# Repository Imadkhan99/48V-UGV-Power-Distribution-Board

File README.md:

# 48V-UGV-Power-Distribution-Board
48 V high-current power distribution PCB for a 4-wheel UGV, featuring MOSFET high-side switching and a two-layer KiCad design.
# 48 V UGV Power Distribution Board

### Project Overview

This project focuses on the electrical design and PCB layout of a high-current Power Distribution Board (PDB) for a four-wheel autonomous Unmanned Ground Vehicle (UGV) intended for vineyard applications.

The objective is to develop a compact power distribution architecture capable of supplying multiple motor controllers and auxiliary loads from a nominal 48 V battery system.

### Key Design Specifications

| Parameter | Design Target |
|---|---|
| Input Voltage | 48 V DC nominal |
| System Power | Approximately 5 kW |
| Maximum Bus Current | 100 A |
| Motor Controller Channels | 4 |
| Switching Architecture | P-channel MOSFET high-side switching |
| MOSFET | Vishay SUM70101EL-GE3 |
| Gate Control | Discrete BJT driver |
| PCB Configuration | 2 layers, 200 × 100 mm |
| Design Software | KiCad 9 |

### Engineering Focus

- Design of high-current DC power distribution circuits.
- Implementation of discrete MOSFET switching architecture.
- High-current PCB routing and copper-zone design.
- Component selection based on electrical requirements.
- Connector placement and power/ground layout.
- Thermal management considerations and via stitching.

### Development Status

**Design-stage project:** Initial PCB layout and routing have been completed. Formal electrical verification, fabrication, thermal validation, and hardware testing are not yet documented.

The published specifications represent design objectives rather than verified hardware ratings.

### Tools and Technologies

KiCad 9, Power Electronics, PCB Layout, MOSFET Switching, DC Power Distribution, and Robotics Electrical Systems.

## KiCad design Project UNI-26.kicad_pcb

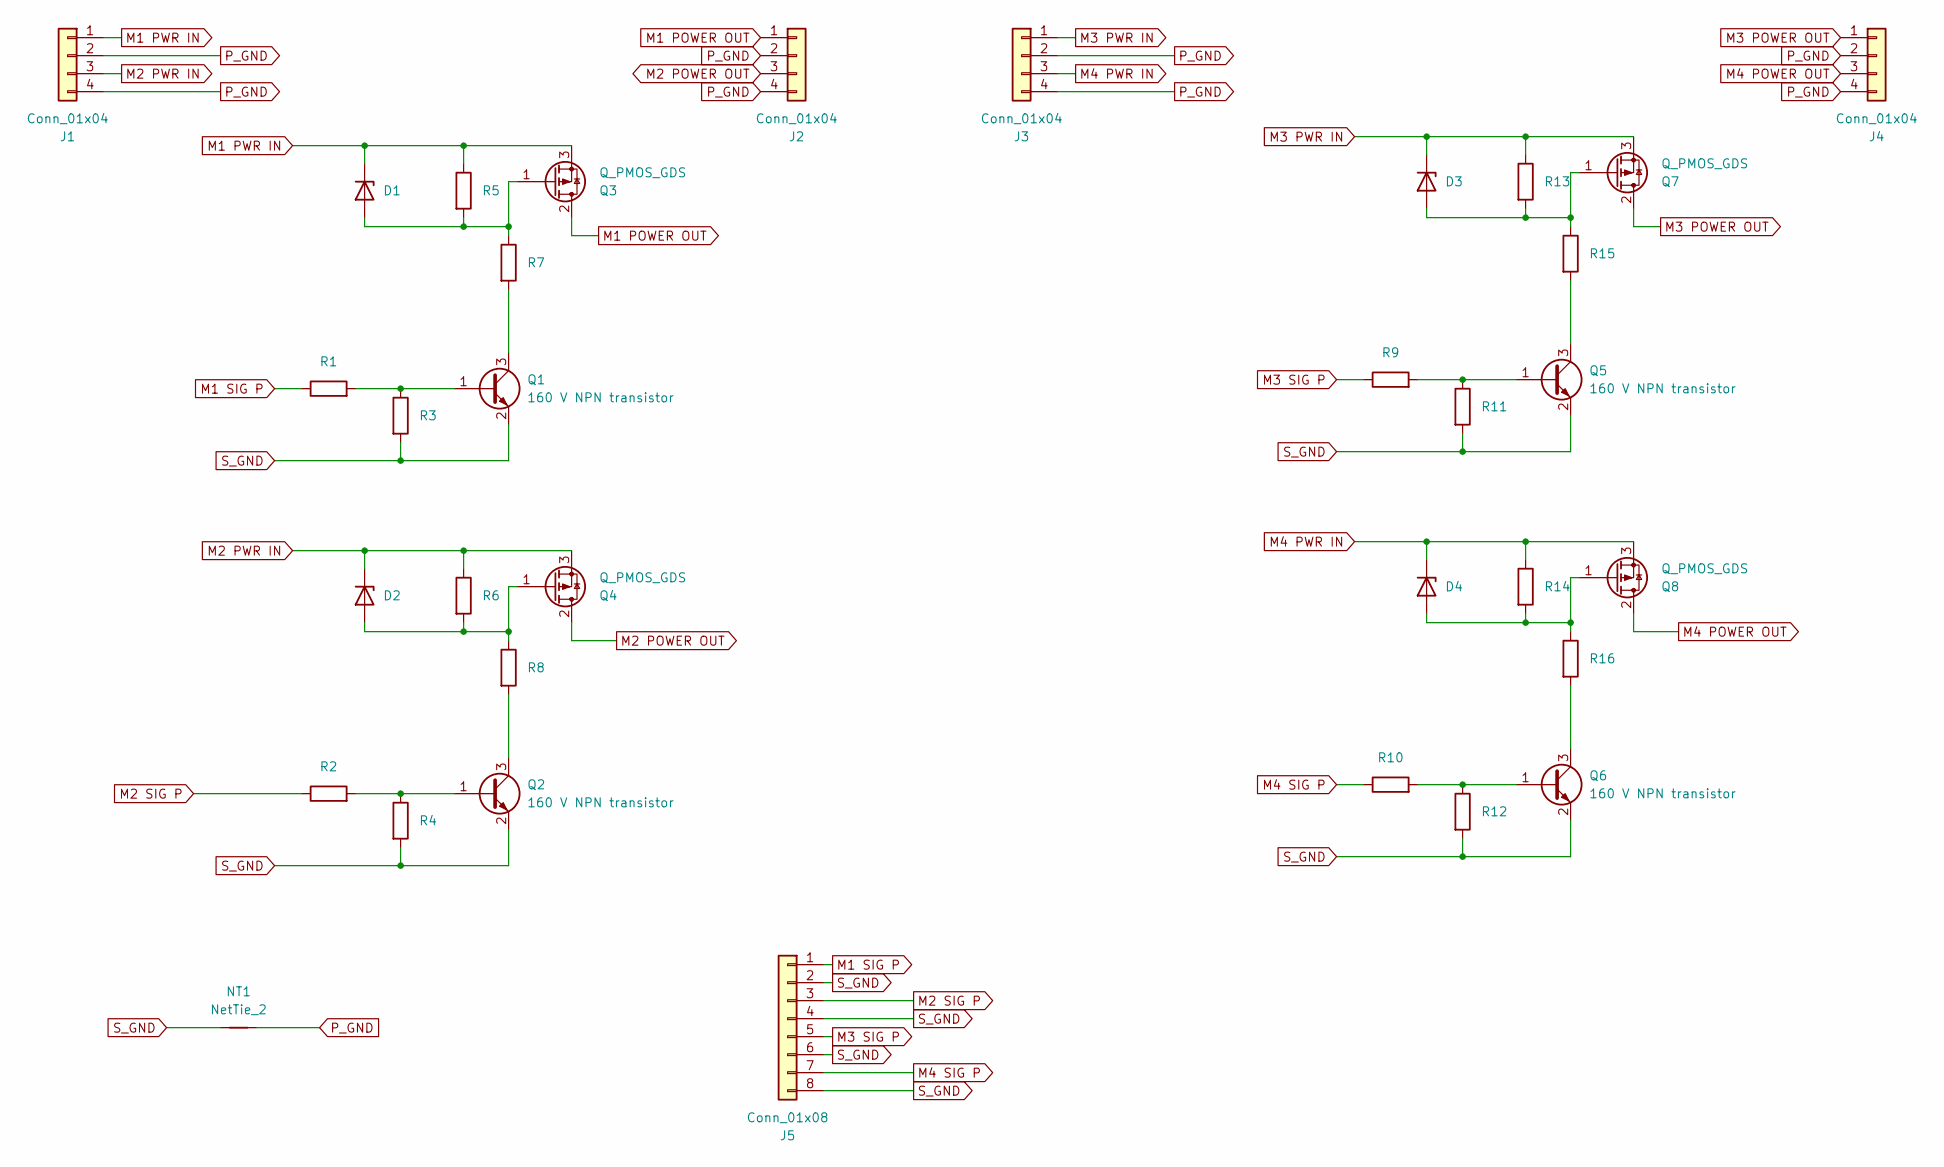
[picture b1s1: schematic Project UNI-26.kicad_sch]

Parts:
D1, D2, D3, D4: 12 V, 500 mW Zener; D_SOD-123; Manufacturer Part No. BZT52C12-7-F
J1, J2, J3, J4: Conn_01x04; 1716866; Manufacturer Part No. 1716866
J5: Conn_01x08; JST_GH_SM08B-GHS-TB_1x08-1MP_P1.25mm_Horizontal
NT1: NetTie_2; NetTie-2_SMD_Pad0.5mm
Q1, Q2, Q5, Q6: 160 V NPN transistor; SOT-23
Q3, Q4, Q7, Q8: Q_PMOS_GDS; TO-263-3_TabPin2
R1, R2, R9, R10: 2.2 kΩ, 1%, 0.125 W; R_0805_2012Metric; Manufacturer Part No. RC0805FR-072K2L
R3, R4, R11, R12: 100 kΩ, 1%, 0.125 W; R_0805_2012Metric; Manufacturer Part No. RC0805FR-07100KL
R5, R6, R13, R14: 47 kΩ, 1%, 0.125 W; R_0805_2012Metric; Manufacturer Part No. RC0805FR-0747KL
R7, R8, R15, R16: 10 kΩ, 1%, 1 W; R_2512_6332Metric; Manufacturer Part No. RC2512FK-0710KL

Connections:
M1 POWER OUT: J2.1, Q3.2 (D)
M1 PWR IN: D1.1 (K), J1.1, Q3.3 (S), R5.1
M1 SIG P: J5.1, R1.1
M2 POWER OUT: J2.3, Q4.2 (D)
M2 PWR IN: D2.1 (K), J1.3, Q4.3 (S), R6.1
M2 SIG P: J5.3, R2.1
M3 POWER OUT: J4.1, Q7.2 (D)
M3 PWR IN: D3.1 (K), J3.1, Q7.3 (S), R13.1
M3 SIG P: J5.5, R9.1
M4 POWER OUT: J4.3, Q8.2 (D)
M4 PWR IN: D4.1 (K), J3.3, Q8.3 (S), R14.1
M4 SIG P: J5.7, R10.1
unnamed: D1.2 (A), Q3.1 (G), R5.2, R7.1
unnamed: D2.2 (A), Q4.1 (G), R6.2, R8.1
unnamed: D3.2 (A), Q7.1 (G), R13.2, R15.1
unnamed: D4.2 (A), Q8.1 (G), R14.2, R16.1
unnamed: Q1.1 (B), R1.2, R3.1
unnamed: Q1.3 (C), R7.2
unnamed: Q2.1 (B), R2.2, R4.1
unnamed: Q2.3 (C), R8.2
unnamed: Q5.1 (B), R9.2, R11.1
unnamed: Q5.3 (C), R15.2
unnamed: Q6.1 (B), R10.2, R12.1
unnamed: Q6.3 (C), R16.2
P_GND: J1.2, J1.4, J2.2, J2.4, J3.2, J3.4, J4.2, J4.4, NT1.2
S_GND: J5.2, J5.4, J5.6, J5.8, NT1.1, Q1.2 (E), Q2.2 (E), Q5.2 (E), Q6.2 (E), R3.2, R4.2, R11.2, R12.2

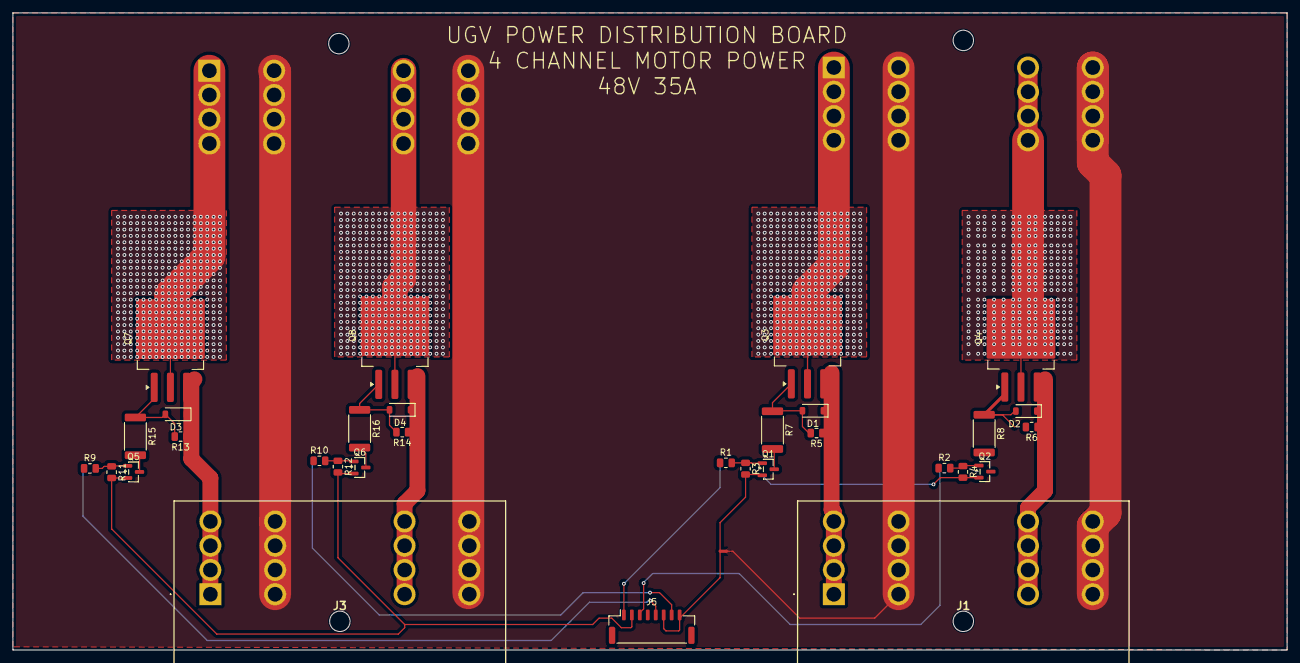
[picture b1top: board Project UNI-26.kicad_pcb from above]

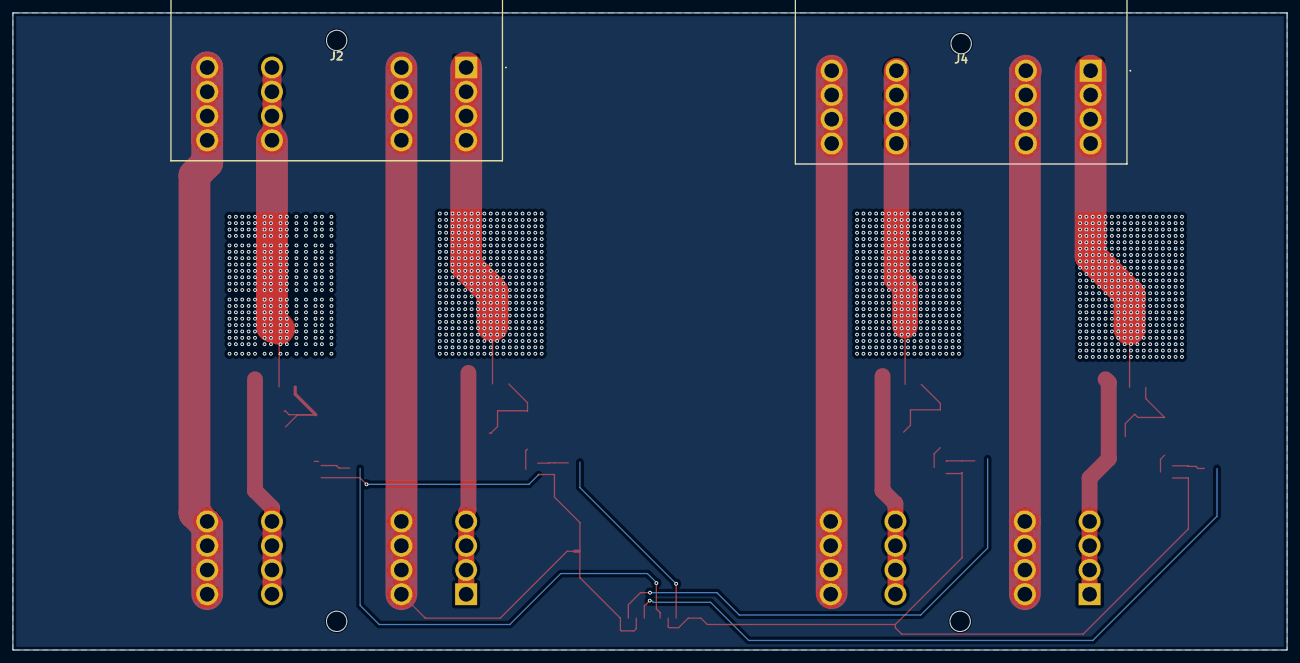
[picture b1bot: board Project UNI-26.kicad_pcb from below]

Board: 2 copper layers, 200.0 x 100.0 mm, 34 parts (2 on the bottom side), 26 nets.
